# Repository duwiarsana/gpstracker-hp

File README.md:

# GPS GPRS SMS Tracker

Proyek ini menggunakan **modul GPS dan GPRS (GSM)** secara terpisah untuk mengirimkan koordinat lokasi via SMS ketika menerima perintah dari pengguna. Koding ini dibuat khusus untuk PCB yang sudah dicetak dalam proyek ini.

## 📌 Deskripsi Proyek

Kode ini bekerja dengan membaca data dari modul **GPS** dan mengirimkan koordinat melalui **modul GPRS (GSM)** dalam bentuk link Google Maps. Saat perangkat menerima SMS dengan kata kunci **"LOKASI"**, maka akan membalas dengan tautan lokasi GPS terbaru.

Selain mengirimkan lokasi melalui SMS, proyek ini juga memiliki fitur **panggilan suara**. Jika nomor yang terhubung dengan modul GSM melakukan panggilan ke perangkat ini, maka panggilan akan **otomatis diangkat pada dering ketiga**.

Proyek ini masih berbasis SMS, tetapi jika ingin mengembangkan sistem dengan mengirim data ke **server atau internet**, bisa dilakukan update coding dengan menggunakan **basis data GPRS**.

## 🛠️ Hardware yang Digunakan

- **Mikrokontroler**: Arduino (contoh: Arduino Uno, Nano, atau lainnya)
- **Modul GPS**: Neo-6M atau kompatibel
- **Modul GSM/GPRS**: SIM800L atau SIM900
- **PCB Custom**: Koding ini dibuat untuk PCB khusus yang sudah dirancang agar sesuai dengan proyek ini
- **Kartu SIM** dengan pulsa untuk mengirim SMS dan melakukan panggilan

## 🖇️ **Koneksi Hardware** (Jika Menggunakan Arduino dengan Modul GPS & GSM Terpisah)

Jika kamu menggunakan Arduino tanpa PCB khusus, pastikan koneksi berikut:

### **Modul GPS (Neo-6M)**

| GPS Pin | Arduino Pin |
| ------- | ----------- |
| VCC     | 5V          |
| GND     | GND         |
| TX      | D3          |
| RX      | D2          |

### **Modul GSM (SIM800L/SIM900)**

| GSM Pin | Arduino Pin                            |
| ------- | -------------------------------------- |
| VCC     | 5V (Gunakan regulator 4.2V jika perlu) |
| GND     | GND                                    |
| TX      | D5                                     |
| RX      | D4                                     |

> **Catatan:** Jika menggunakan PCB khusus yang sudah dicetak, koneksi sudah diatur secara langsung dalam desain PCB, jadi tidak perlu kabel tambahan.

## 🔧 Library yang Digunakan

Sebelum meng-compile kode, pastikan kamu sudah menginstal library berikut di **Arduino IDE**:

- **[TinyGPS++](https://github.com/mikalhart/TinyGPSPlus)** → Untuk membaca data dari GPS
- **SoftwareSerial** (bawaan Arduino) → Untuk komunikasi serial dengan modul GSM & GPS

## ⚙️ Cara Kerja

1. **Perangkat menyala** dan mulai membaca data GPS.
2. Saat menerima SMS dengan isi **"LOKASI"**, perangkat akan mengambil data koordinat dari GPS.
3. Data latitude dan longitude akan diubah menjadi link Google Maps.
4. SMS akan dikirim kembali ke pengirim dengan format: https://maps.google.com/?q=latitude,longitude
5. Nomor pengirim SMS akan disimpan sementara untuk membalas otomatis.
6. Setelah mengirim SMS, perangkat menghapus pesan yang diterima agar memori tidak penuh.
7. Jika ada **panggilan masuk**, perangkat akan **otomatis mengangkat pada dering ketiga**.

## 📌 Cara Menggunakan

1. **Siapkan PCB yang sudah dirakit** dengan Arduino dan modul GPS/GSM.
2. **Masukkan kartu SIM ke modul GSM** (pastikan memiliki pulsa atau paket SMS).
3. **Upload kode ke Arduino** menggunakan Arduino IDE.
4. **Kirim SMS berisi "LOKASI"** ke nomor yang ada di modul GSM.
5. **Perangkat akan membalas dengan link lokasi** berdasarkan data dari modul GPS.
6. **Lakukan panggilan ke nomor SIM pada modul GSM**, dan perangkat akan **mengangkat otomatis pada dering ketiga**.

## 🔥 Troubleshooting

Jika tidak mendapatkan SMS balasan atau koordinat tidak muncul:

- **Cek power supply modul GSM** (SIM800L biasanya butuh minimal 2A agar stabil).
- **Pastikan modul GPS mendapatkan sinyal satelit** (gunakan di luar ruangan untuk tes awal).
- **Gunakan serial monitor** di Arduino IDE untuk melihat output debug.

## 📜 Lisensi

Proyek ini menggunakan lisensi MIT, yang berarti bebas digunakan, dimodifikasi, dan didistribusikan.

---

🚀 Selamat mencoba! Jika ada pertanyaan atau ingin menggunakan PCB khusus ini, silakan hubungi saya.

## 💖 Dukung Pengembangan Proyek Ini

Jika kamu merasa proyek ini bermanfaat dan ingin mendukung pengembangan lebih lanjut, kamu bisa memberikan **donasi melalui Saweria**:

🔗 [https://saweria.co/duwiarsana](https://saweria.co/duwiarsana)  

Terima kasih atas dukungannya! 🤗

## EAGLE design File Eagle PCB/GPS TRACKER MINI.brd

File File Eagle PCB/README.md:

# README FILE EAGLE PCB GPS Tracker Mini

## Deskripsi Proyek
GPS Tracker Mini adalah proyek pelacak GPS berbasis **ATmega328P**, **SIM800C**, dan **Quectel L80 GNSS**. Proyek ini memungkinkan pelacakan lokasi secara real-time dengan komunikasi GSM/GPRS.

### Fitur Utama:
- **Pelacakan GPS:** Menggunakan modul **Quectel L80** untuk mendapatkan koordinat lokasi secara akurat.
- **Koneksi GSM:** Memanfaatkan modul **SIM800C** untuk mengirimkan data lokasi melalui SMS atau server berbasis GPRS.
- **Microcontroller ATmega328P:** Sebagai pusat kendali dari perangkat.
- **Slot MicroSD:** Untuk menyimpan log data lokasi jika koneksi tidak tersedia.
- **Konektor U.FL:** Untuk penggunaan antena eksternal pada modul GSM.

## Skema dan Desain PCB
Desain perangkat ini dibuat menggunakan **Eagle PCB** dan terdiri dari dua file utama:
- **Schematic:** [`GPS TRACKER MINI.sch`](./GPS%20TRACKER%20MINI.sch)
- **PCB Layout:** [`GPS TRACKER MINI.brd`](./GPS%20TRACKER%20MINI.brd)

## Skema Kalau Pakai Arduino Uno dan GPS NEO

## Bill of Materials (BOM)
Berikut adalah daftar komponen utama yang digunakan dalam proyek ini:

| Qty | Value | Device | Package | Parts |
|----|------|--------|---------|-------|
| 1  | ATMEGA328P-MU | ATMEGA328P-MU | QFN-32 | U1 |
| 1  | SIM800C | SIM800C | LCC-42 | U2 |
| 1  | L80_GNSS_MODULE | L80 GNSS Module | Custom | U3 |
| 1  | 4050D | Hex Buffer | SO16 | IC1 |
| 1  | LP298-33 | LDO Regulator 3.3V | SOT23-5L | IC2 |
| 1  | MICROSD | MicroSD Card Slot | MICROSD | X1 |
| 1  | ZD-SOD123 | 5.1V Zener Diode | SOD123 | ZD1 |
| 4  | 0.1uF | Capacitor | C0603 | C3, C15, C19, C21 |
| 2  | 100uF | Capacitor | B/3528-21R | C4, C5 |
| 1  | 10K | Resistor | R0603 | R1 |
| 1  | CSTCE16M0V53MU | Ceramic Resonator 16MHz | CSTCE16M0V53 | Y1 |
| 1  | SIM8051-6-0-14-01-X | Nano SIM Card Connector | SMT | J1 |
| 1  | CON-HIROSE-COAXIAL-U.FL | U.FL Connector | SMT | GSM |
| 1  | LED (Red) | Indicator | LED0805 | ACT |
| 1  | LED (Blue) | Indicator | LED0805 | LED4 |

## Instalasi dan Penggunaan
1. **Flash Firmware** ke ATmega328P menggunakan Arduino IDE atau PlatformIO.
2. **Sambungkan Antena** ke konektor U.FL untuk sinyal GSM lebih baik.
3. **Masukkan Kartu SIM** dan pastikan memiliki paket data aktif.
4. **Gunakan Software** untuk membaca koordinat GPS yang dikirim via SMS atau HTTP POST.

## Pemesanan PCB & Donasi
Jika kamu ingin membeli PCB dari proyek ini atau mendukung pengembangannya, silakan hubungi saya melalui WhatsApp:  
📲 **[085738244251](https://wa.me/6285738244251)**

Atau bisa juga berdonasi melalui:  

## Lisensi
Proyek ini berlisensi **MIT License**, artinya bebas digunakan dan dimodifikasi, namun tetap mencantumkan atribusi kepada pembuat asli.

---
Jika ada pertanyaan atau saran, jangan ragu untuk menghubungi saya melalui GitHub atau media sosial lainnya!

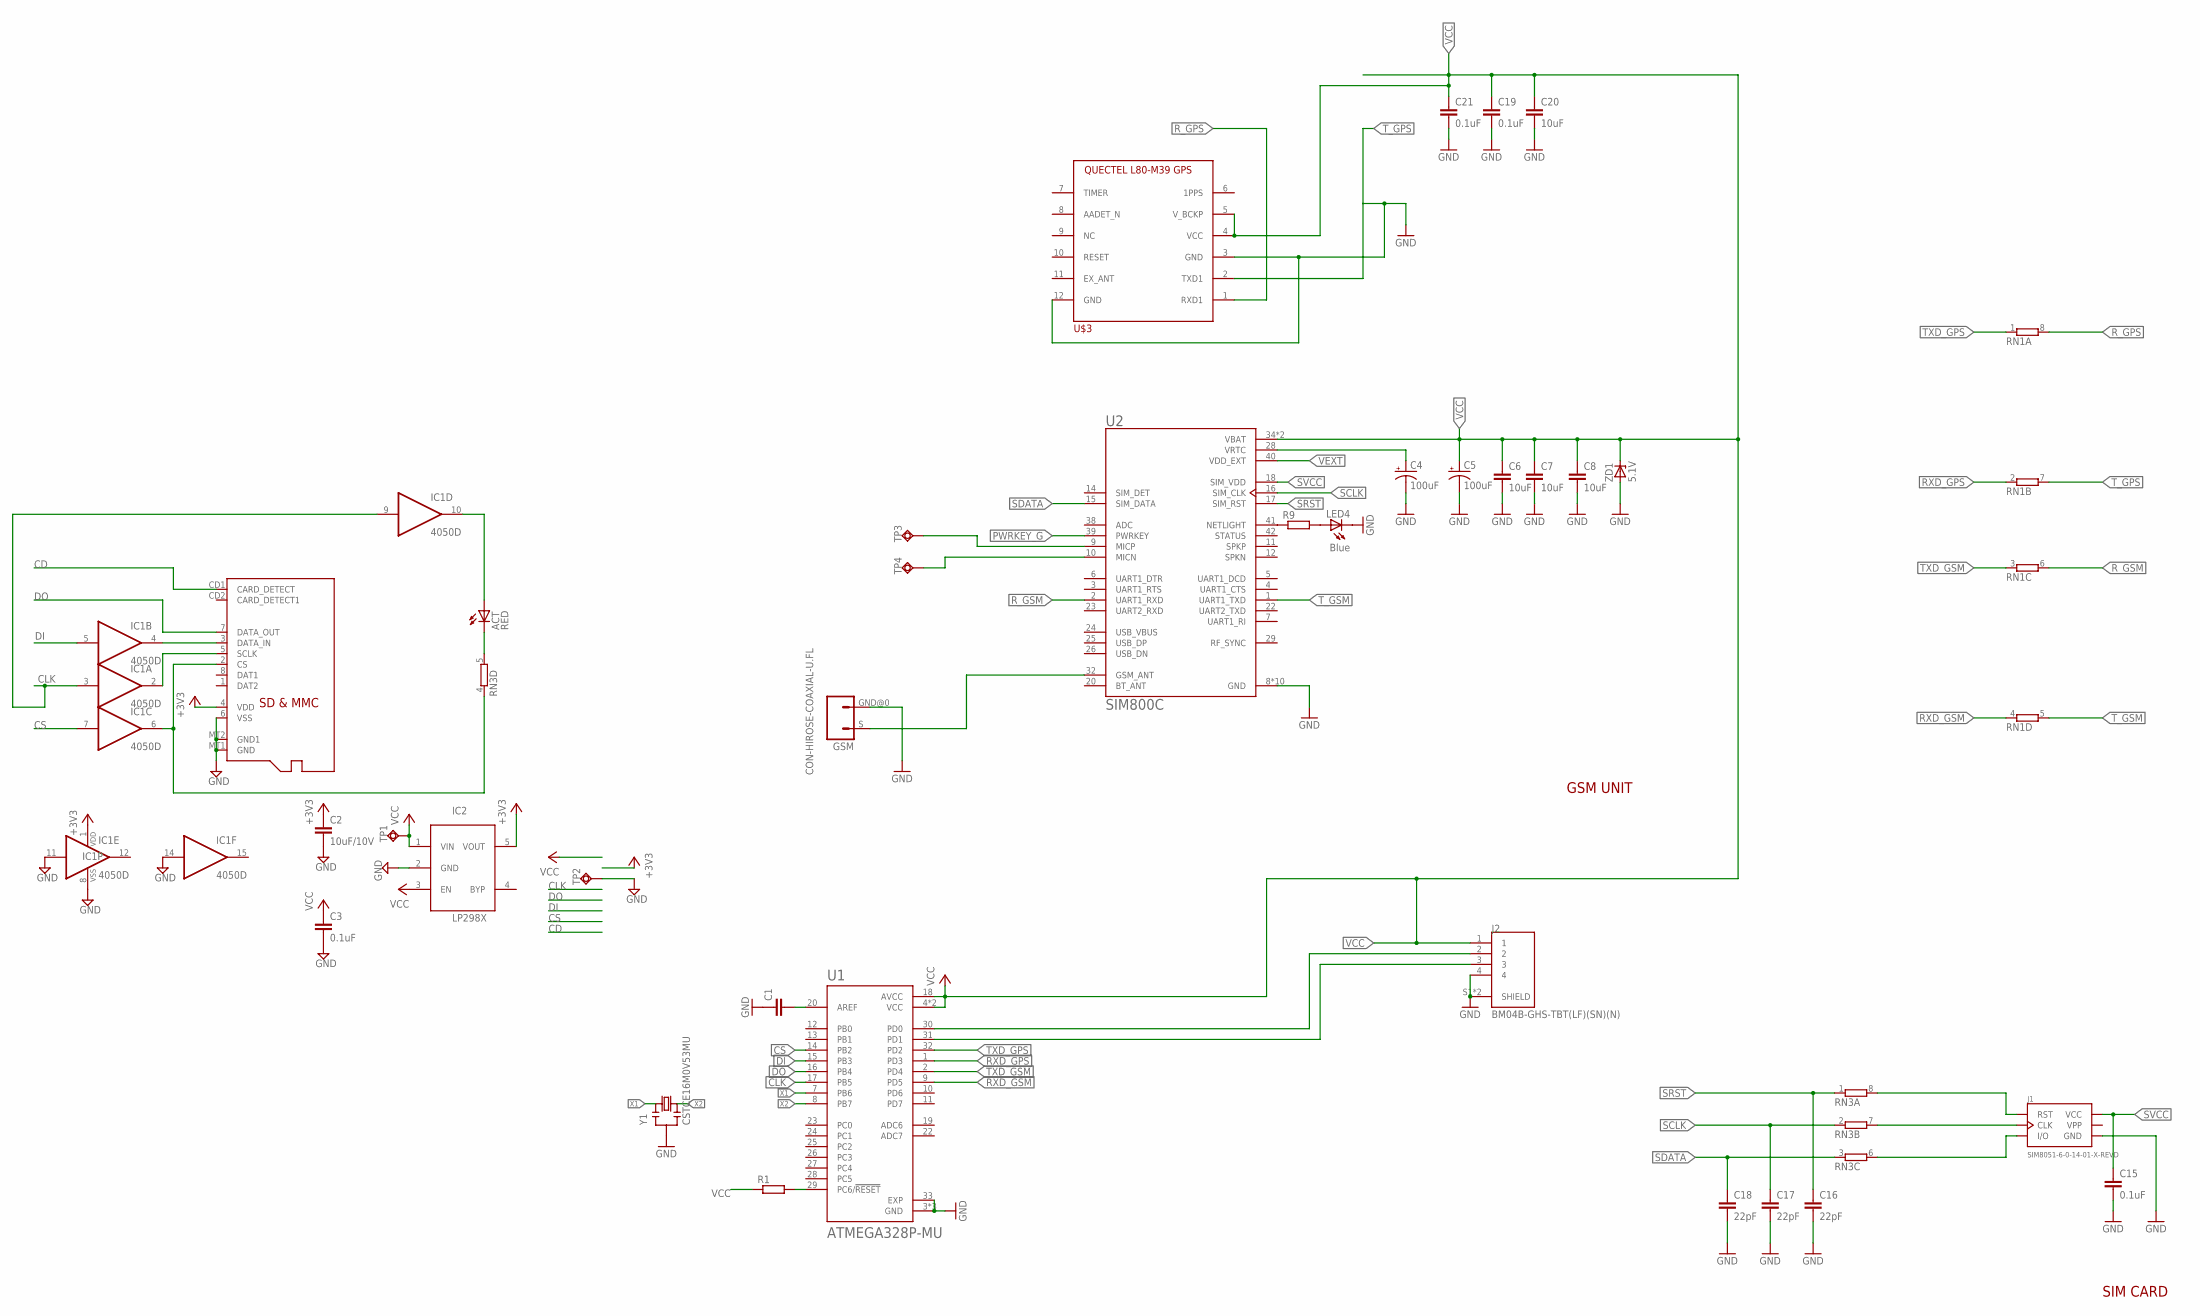
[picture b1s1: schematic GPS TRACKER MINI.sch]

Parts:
ACT: RED; CHIP-LED0805
C1: C-EUC0603K; C0603K
C2: 10uF/10V; C0603
C3, C15, C19, C21: 0.1uF; C0603
C4, C5: 100uF; B/3528-21R
C6, C7, C8, C20: 10uF; C0603
C16, C17, C18: 22pF; C0603
GSM: CON-HIROSE-COAXIAL-U.FL; CON-U.FL
IC1: 4050D; SO16
IC2: LP298XS; SOT23-5L
J1: SIM8051-6-0-14-01-X-REVD; GCT_SIM8051-6-0-14-01-X-REVD
J2: BM04B-GHS-TBT(LF)(SN)(N); JST_BM04B-GHS-TBT(LF)(SN)(N)
LED4: Blue; CHIP-LED0805
R1, R9: R-EU_R0603; R0603
RN1, RN3: 4R-N0603-ARC; 0603-ARC
TP1, TP2: TPSQTP20R; TP20R
TP3, TP4: TPSQTP14R; TP14R
U1: ATMEGA328P-MU; QFN50P500X500X100-33N
U2: SIM800C; LCC110P1570X1760X250-42N
U$3: L80_GNSS_MODULE; L80_PACKAGE
X1: MICROSD
Y1: CSTCE16M0V53MU; CSTCE16M0V53
ZD1: 5.1V; SOD123

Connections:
+3V3: C2.1, IC1.1 (VDD), IC2.5 (VOUT), X1.4 (VDD)
CD: X1.CD1 (CARD_DETECT)
CLK: IC1.3 (I), IC1.9 (I), U1.17 (PB5)
CS: IC1.7 (I), U1.14 (PB2)
DI: IC1.5 (I), U1.15 (PB3)
DO: U1.16 (PB4), X1.7 (DATA_OUT)
GND: C1.1, C2.2, C3.2, C4.-, C5.-, C6.2, C7.2, C8.2, C15.2, C16.2, C17.2, C18.2, C19.2, C20.2, C21.2, GSM.GND@0 (2), IC1.8 (VSS), IC1.11 (I), IC1.14 (I), IC2.2 (GND), J1.C5 (GND), J2.4, J2.S1 (SHIELD), J2.S2 (SHIELD), LED4.C, TP2.TP, U1.3 (GND), U1.5 (GND), U1.21 (GND), U1.33 (EXP), U2.8 (GND), U2.13 (GND), U2.19 (GND), U2.21 (GND), U2.27 (GND), U2.30 (GND), U2.31 (GND), U2.33 (GND), U2.36 (GND), U2.37 (GND), U$3.3 (GND), U$3.12 (GND), X1.6 (VSS), X1.MT1 (GND), X1.MT2 (GND1), Y1.2, ZD1.A
unnamed: ACT.A, IC1.10 (O)
unnamed: C1.2, U1.20 (AREF)
unnamed: IC1.2 (O), X1.5 (SCLK)
unnamed: IC1.6 (O), RN3.4 (1), X1.2 (CS)
unnamed: ACT.C, RN3.5 (2)
unnamed: IC1.4 (O), X1.3 (DATA_IN)
unnamed: R9.1, U2.41 (NETLIGHT)
unnamed: LED4.A, R9.2
unnamed: J2.2, U1.30 (PD0)
unnamed: J2.3, U1.31 (PD1)
unnamed: TP3.TP, U2.9 (MICP)
unnamed: TP4.TP, U2.10 (MICN)
unnamed: R1.2, U1.29 (PC6/!RESET)
unnamed: C4.+, U2.28 (VRTC)
unnamed: GSM.S (1), U2.32 (GSM_ANT)
unnamed: J1.C2 (RST), RN3.8 (2)
unnamed: J1.C3 (CLK), RN3.7 (2)
unnamed: J1.C7 (I/O), RN3.6 (2)
PWRKEY_G: U2.39 (PWRKEY)
RXD_GPS: RN1.2 (1), U1.1 (PD3)
RXD_GSM: RN1.4 (1), U1.9 (PD5)
R_GPS: RN1.8 (2), U$3.1 (RXD1)
R_GSM: RN1.6 (2), U2.2 (UART1_RXD)
SCLK: C17.1, RN3.2 (1), U2.16 (SIM_CLK)
SDATA: C18.1, RN3.3 (1), U2.15 (SIM_DATA)
SRST: C16.1, RN3.1, U2.17 (SIM_RST)
SVCC: C15.1, J1.C1 (VCC), U2.18 (SIM_VDD)
TXD_GPS: RN1.1, U1.32 (PD2)
TXD_GSM: RN1.3 (1), U1.2 (PD4)
T_GPS: RN1.7 (2), U$3.2 (TXD1)
T_GSM: RN1.5 (2), U2.1 (UART1_TXD)
VCC: C3.1, C5.+, C6.1, C7.1, C8.1, C19.1, C20.1, C21.1, IC2.1 (VIN), IC2.3 (EN), J2.1, R1.1, TP1.TP, U1.4 (VCC), U1.6 (VCC), U1.18 (AVCC), U2.34 (VBAT), U2.35 (VBAT), U$3.4 (VCC), U$3.5 (V_BCKP), ZD1.C
VEXT: U2.40 (VDD_EXT)
VPP: J1.C6 (VPP)
X1: U1.7 (PB6), Y1.1
X2: U1.8 (PB7), Y1.3

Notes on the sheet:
GSM UNIT
SIM CARD

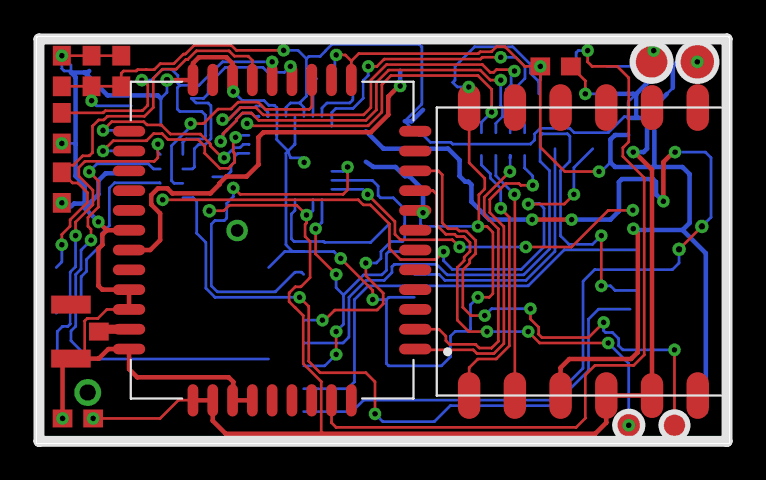
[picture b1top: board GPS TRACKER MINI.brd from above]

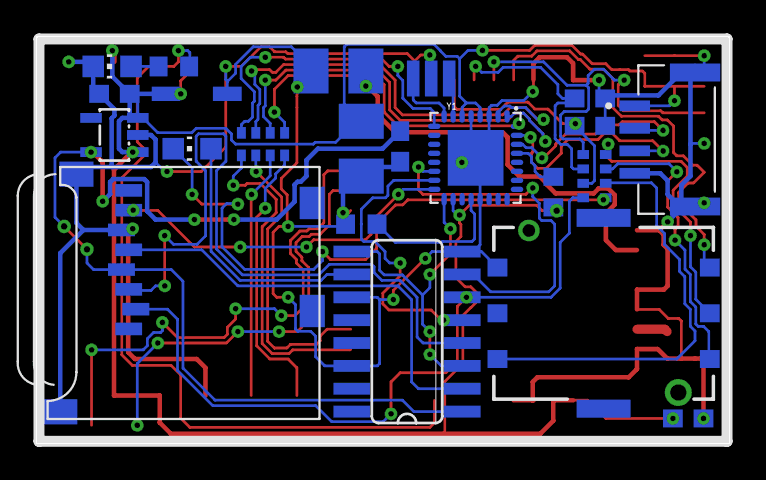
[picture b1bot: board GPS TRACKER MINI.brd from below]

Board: 2 copper layers, 38.5 x 22.6 mm, 36 parts (22 on the bottom side), 39 nets.

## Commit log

2025-03-04 Update gpstrackeryoutube.ino
    Menambahkan keterangan coding dan mengubah pin komunikasi sesuai dengan design PCB
2025-03-10 Menambahkan file design EAGLE PCB
2025-03-10 Update README.md
    menambahkan gambar rangkaian kalau menggunakan arduino
2025-03-10 Update README.md
    perbaikan link gambar

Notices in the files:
parts and their libraries:
m-pad-2.1: License : GNU General Public License version 2 (see bottom)
SparkFun: Licensing: CC v3.0 Share-Alike You are welcome to use this library for commercial purposes.
